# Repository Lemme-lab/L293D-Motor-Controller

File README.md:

# L293D-Motor-Controller
A motor controller based on the L293D chip. Some extra indicators are added.

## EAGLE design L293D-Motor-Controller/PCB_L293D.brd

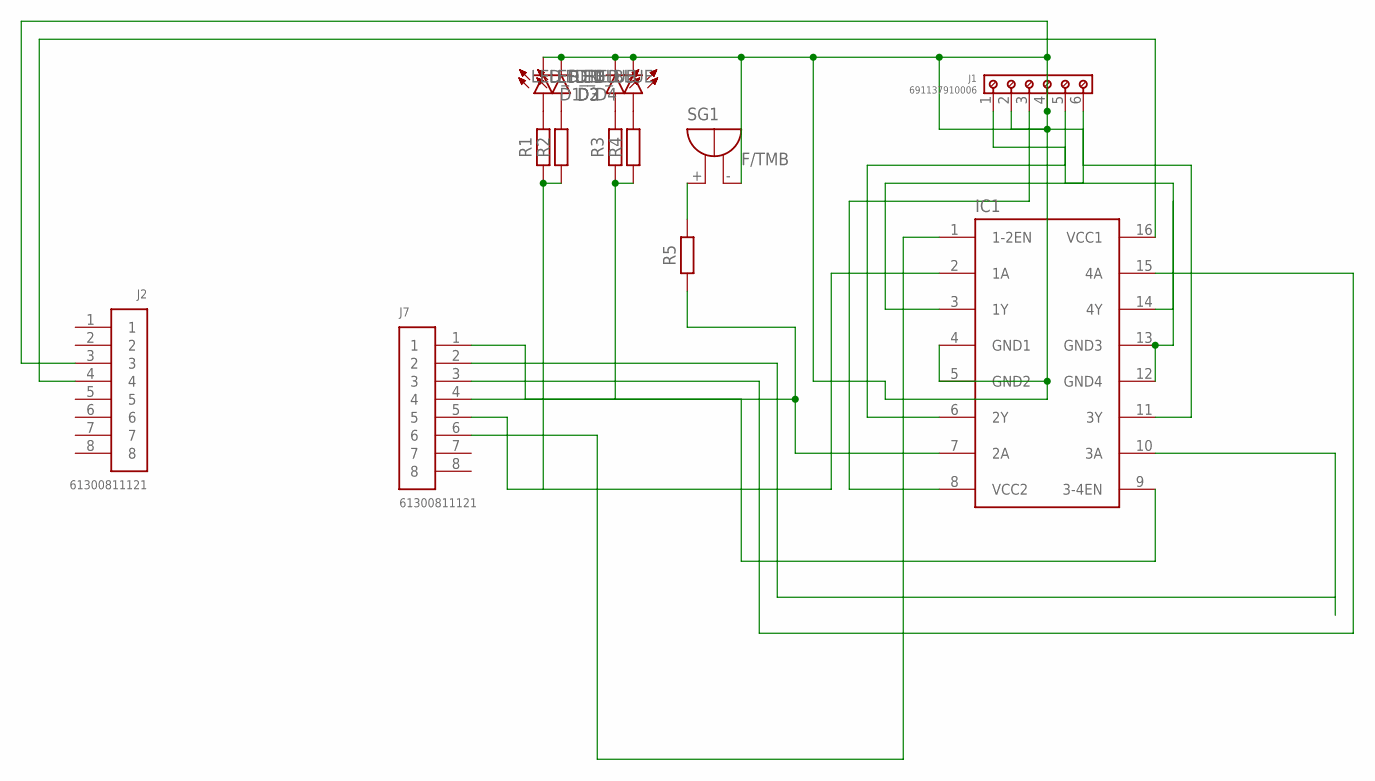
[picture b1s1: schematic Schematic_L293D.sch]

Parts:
D1, D2: LED_BLUE; LEDRD254W60D565H860B_B
D3, D4: LED_RED; LEDRD254W60D565H860B
IC1: L293D; DIL16
J1: 691137910006
J2, J7: 61300811121
R1, R2, R3, R4: R_AXIAL-11.7MM-PITCH; RESAD1176W63L850D250B
R5: R_AXIAL-7.2MM-PITCH; RESAD724W46L381D178B
SG1: F/TMB

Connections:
unnamed: IC1.2 (1A), J7.5, R1.1, R2.1
unnamed: IC1.3 (1Y), J1.6
unnamed: IC1.14 (4Y), J1.1
unnamed: IC1.11 (3Y), J1.2
unnamed: IC1.16 (VCC1), J2.4
unnamed: IC1.12 (GND4), IC1.13 (GND3)
unnamed: IC1.6 (2Y), J1.5
unnamed: D1.1 (A), R1.2
unnamed: D2.1 (A), R2.2
unnamed: IC1.15 (4A), J7.3
unnamed: IC1.10 (3A), J7.2
unnamed: D3.1 (A), R3.2
unnamed: D4.1 (A), R4.2
unnamed: IC1.9 (3-4EN), J7.1
unnamed: IC1.1 (1-2EN), J7.6
unnamed: D1.2 (C), D2.2 (C), D3.2 (C), D4.2 (C), IC1.4 (GND1), IC1.5 (GND2), J1.4, J2.3, SG1.-
unnamed: IC1.8 (VCC2), J1.3
unnamed: IC1.7 (2A), J7.4, R3.1, R4.1, R5.1
unnamed: R5.2, SG1.+

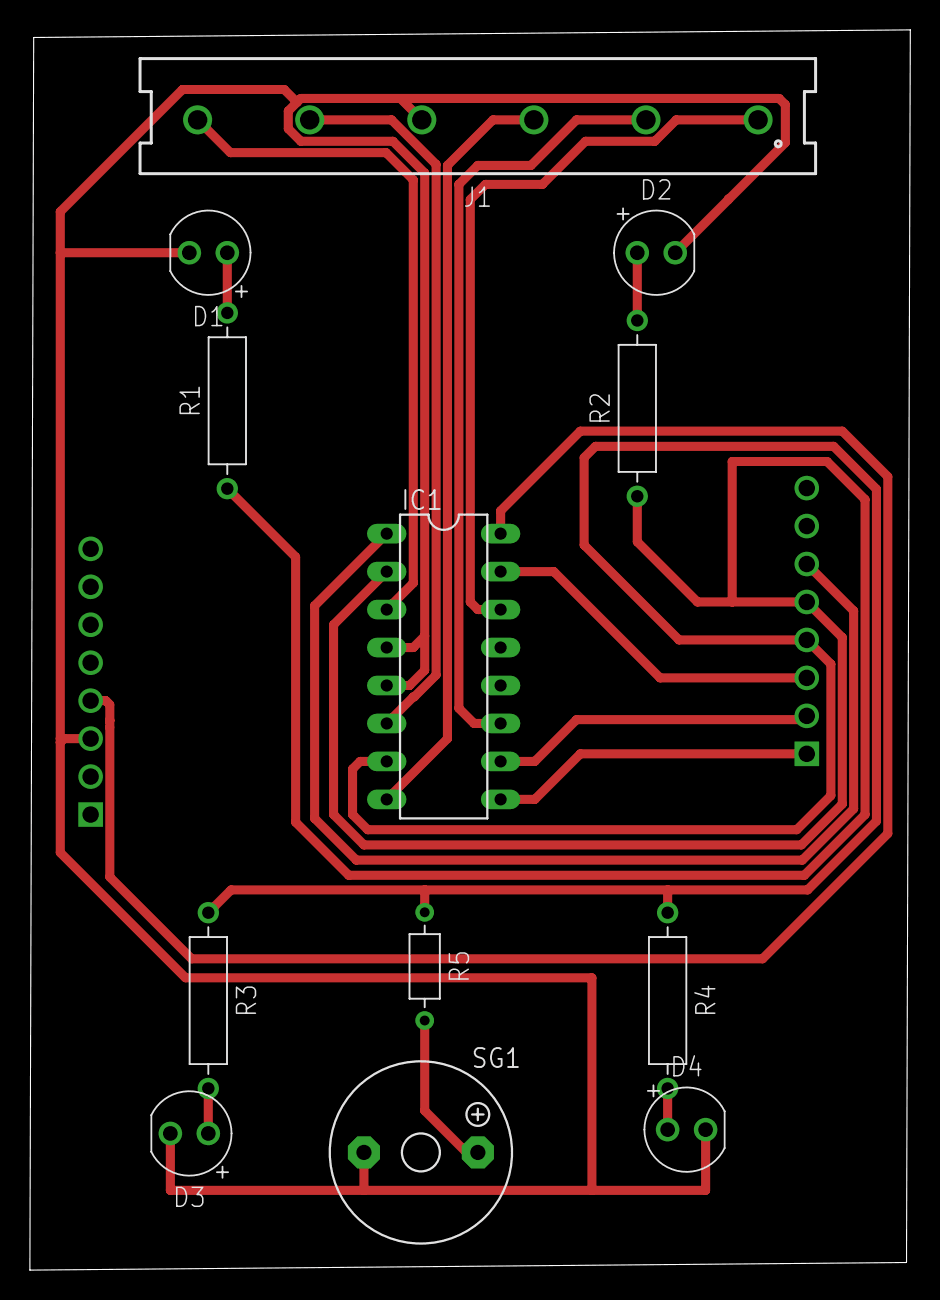
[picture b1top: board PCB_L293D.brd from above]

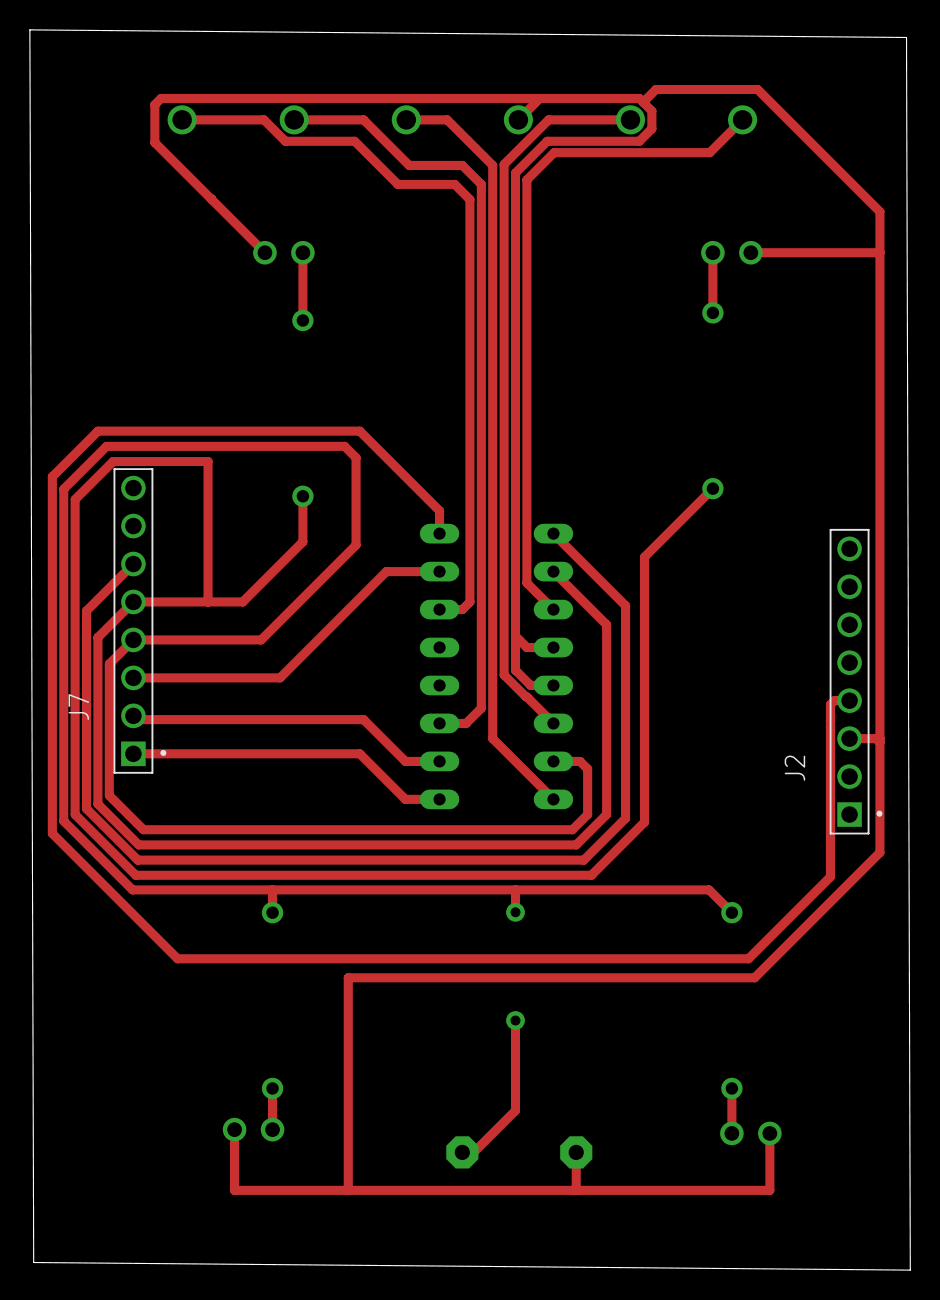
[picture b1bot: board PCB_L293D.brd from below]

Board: 2 copper layers, 58.9 x 83.0 mm, 14 parts (2 on the bottom side), 19 nets.

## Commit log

2021-11-14 init

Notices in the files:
parts and their libraries:
Wurth_Connectors_WR-TBL Wire Protector: Copyright: Würth Elektronik
